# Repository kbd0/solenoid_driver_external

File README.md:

# solenoid_driver_external

A daughterboard for toggling an externally powered solenoid via a 5V signal.  
Uses an optocoupler to isolate the signal-providing circuit from the solenoid circuit.  
  
I made this with the intention of using a USB arduino to control a 12V 3A solenoid powered by a 12V 3A AC adapter from aliexpress.  
  
Currently untested

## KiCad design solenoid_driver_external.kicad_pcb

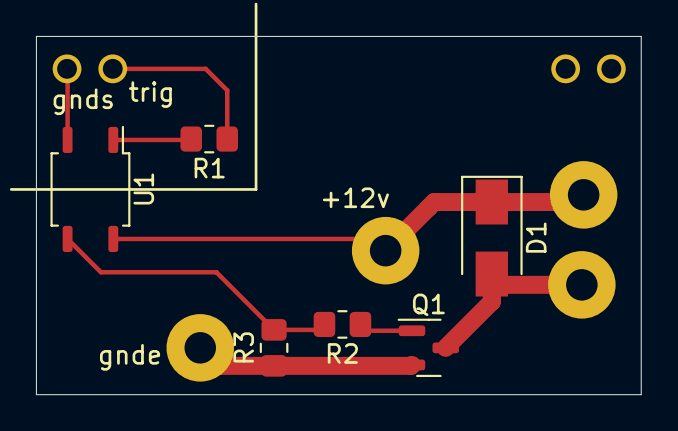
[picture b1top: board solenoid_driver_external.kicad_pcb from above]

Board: 2 copper layers, 33.6 x 19.9 mm, 6 parts (0 on the bottom side), 6 nets.

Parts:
D1: US1M; D_SMA
Q1: AO3400A; SOT-23
R1, R2: 1k; R_0805_2012Metric_Pad1.20x1.40mm_HandSolder
R3: 100k; R_0805_2012Metric_Pad1.20x1.40mm_HandSolder
U1: EL357N(C)(TA)-G; SOP-4_3.8x4.1mm_P2.54mm

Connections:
+12V: D1.1 (K), U1.4
GND: Q1.2 (S), R3.1
unnamed: D1.2 (A), Q1.3 (D)
unnamed: Q1.1 (G), R2.1
unnamed: R1.2, U1.1
unnamed: R2.2, R3.2, U1.3

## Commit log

2023-05-11 init
